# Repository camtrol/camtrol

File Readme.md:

# 캠트롤 Folder back up..

### 1. 2025-03-09-20:42 커밋 내용

- 조명 콘트롤러 저전압 회로 추가.
- 조명 콘트롤러 ST7735 추가.
- 조명 콘트롤러 저전압 진입 동작 추가 (comSend 로 BAT_LOW 보냄) -> while 반복
- 조명 콘트롤러 7" 프로그램 수정 -> BAT_LOW 수신하여 처리.

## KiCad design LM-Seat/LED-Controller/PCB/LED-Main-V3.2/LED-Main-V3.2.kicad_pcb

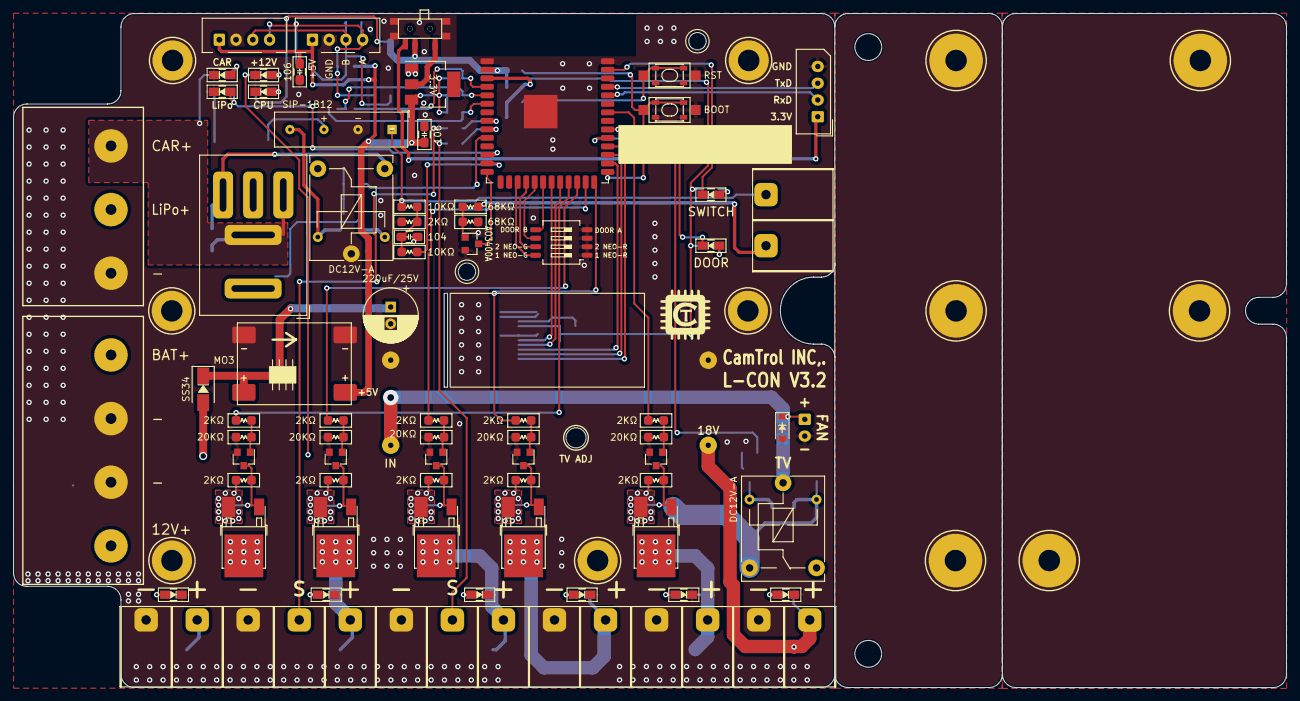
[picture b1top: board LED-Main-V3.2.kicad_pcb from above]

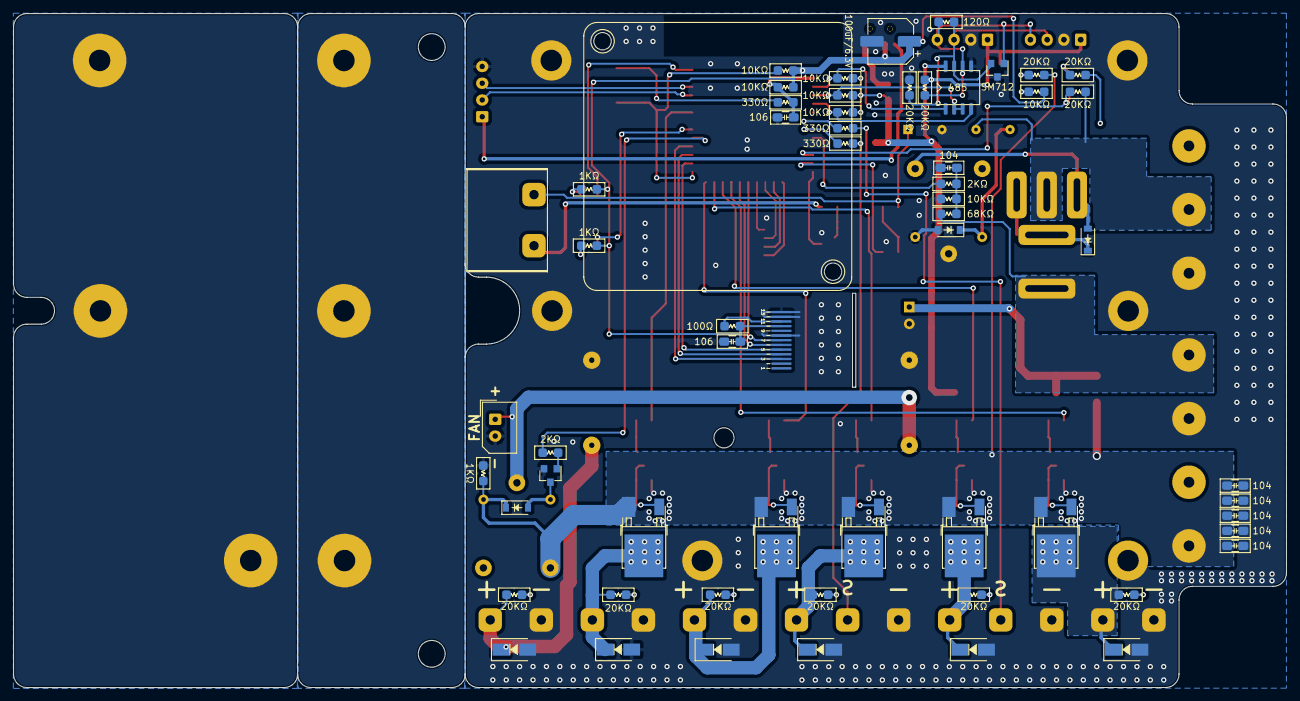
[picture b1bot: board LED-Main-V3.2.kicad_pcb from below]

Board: 2 copper layers, 190.0 x 100.6 mm, 140 parts (57 on the bottom side), 85 nets.

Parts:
C1: 100uF/6.3V; CP_Elec_6.3x5.3
C2, C3, C5, C12: 106; C_0805_HandSoldering
C4: 220uF/25V; CP_Radial_D8.0mm_P2.50mm
C6, C7, C8, C9, C10, C11, C13: 104; C_0805_HandSoldering
D1: CPU; LED_0805
D2, D8, D10, D11, D15, D17, D23, D28: RED LED; LED_0805
D3, D9, D12, D13, D18, D29: 4007; D_SMA
D4, D7, D16, D19: 4007; D_SOD-123
D5: SS34; D_SMA
D6: +12V; LED_0805
D20: LiPo; LED_0805
D21: CAR; LED_0805
D25: SM712; SOT-23
H1, H8, H9, H10, H12: MH; MountingHole_3.2mm_M3-support
H2, H3, H4, H5, H6, H7: MH; MountingHole_3.2mm_M3-pcb
He1: MH; MountingHole_3.2mm_M3-support
J1: 5267-04P; Molex_SPOX_5267-04A_1x04_P2.50mm_Vertical
J2: Conn_01x14_Pin; KF7.62-14P
J3: Conn_01x02_Pin; KF7.62-2P
J4, J11: 5267-04P; XH2.54-4P
J7: 5267-04P; HB-9500-4P
J9: ECH381V-2P; Molex_SPOX_5267-02A_1x02_P2.50mm_Vertical
J15: Conn_01x03_Pin; HB-9500-3P
K1: SIP-1B12; Relay_SPST_StandexMeder_SIL_Form1A
K3, K5: DC12V-A; JQC-T78-DC12V-C
K6: Relay_25A
M1: Fan; 4010-FAN
MO2: STEP-UP
MO3: MP1584; TZT-SMD
Q1, Q2, Q6, Q7, Q10, Q11, Q12, Q13, Q19, Q20: AOD4185; AOD1485
Q3, Q5, Q8, Q9, Q17, Q18: MMBTA42L; SOT-23
Q16: AO3400A; SOT-23
R1, R2, R4, R27, R31, R38, R41, R42, R43: 10KΩ; R_0805_HandSoldering
R3, R24, R26: 330Ω; R_0805_HandSoldering
R5, R8, R9, R14, R16, R17, R20, R21, R29, R30, R37, R52, R54: 2KΩ; R_0805_HandSoldering
R6, R7, R10, R13, R15, R18, R19, R22, R23, R28, R35, R39, R44, R46, R53, R55: 20KΩ; R_0805_HandSoldering
R11, R12, R48: 1KΩ; R_0805_HandSoldering
R25: 100Ω; R_0805_HandSoldering
R32, R33, R47: 68KΩ; R_0805_HandSoldering
R45: 120Ω; R_0805_HandSoldering
ST7735S1: Conn_01x12_Male; ST7735S_IPS
SW2, SW5: SW_Push; TS-3404
SW3: RST; SW_SPST_CK_RS282G05A3
SW4: BOOT; SW_SPST_CK_RS282G05A3
SW7: YSS-1203; SW_DIP_SPSTx04_Slide_Copal_CHS-04A_W5.08mm_P1.27mm_JPin
SW8: NW3-SK-02
U1: 3.3V; SOT-223
U2: ESP32-S3-PCB
U4: 485; MAX485

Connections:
3V3: C1.1, C5.1, R1.1, R2.1, R4.2, R12.1, R25.1, R48.1, ST7735S1.10, SW8.2 (B), U2.2 (3V3)
+5V: C3.1, C12.1, J4.1, J11.1, MO3.4 (+5V), R41.2, R42.2, R43.2, R46.1, U1.3 (VI), U4.8 (VCC)
+12P: C6.2, C7.2, C8.2, C9.2, C10.2, D5.1 (A), D16.2 (K), J7.4, K3.6, K3.14, Q1.S (Source), Q2.S (Source), Q6.S (Source), Q7.S (Source), Q10.S (Source), Q11.S (Source), Q12.S (Source), Q13.S (Source), Q19.S (Source), Q20.S (Source), R5.1, R10.1, R11.2, R14.1, R20.1, R21.1, R54.1
/485-A: D25.1 (A1), J4.4, J11.4, R45.1, R46.2, U4.6 (A)
/485-B: D25.2 (A2), J4.3, J11.3, R44.1, R45.2, U4.7 (B)
/+: J15.2, K1.5, K6.87A, R35.1
BAT +: J7.1, K6.30, R47.2
BOOT: R4.1, SW4.1, SW5.2, U2.27 (IO_0)
DI: R41.1, U2.6 (IO_6), U4.4 (DI)
DOOR: Q16.3 (D), U2.14 (IO_20)
EN: C2.1, R2.2, R3.1, U2.3 (EN)
ENABLE: R42.1, U2.5 (IO_5), U4.2 (~RE), U4.3 (DE)
FLOOR: R52.2, U2.34 (TDI/IO_41)
GNDPWR: C1.2, C2.2, C3.2, C4.2, C5.2, C6.1, C7.1, C8.1, C9.1, C10.1, C11.2, C12.2, C13.2, D1.1 (K), D2.1 (K), D3.1 (A), D4.1 (A), D6.1 (K), D8.1 (K), D9.1 (A), D10.1 (K), D11.1 (K), D12.1 (A), D13.1 (A), D17.1 (K), D18.1 (A), D19.1 (A), D20.1 (K), D21.1 (K), D25.3 (common), D28.1 (K), D29.1 (A), H2.1, H3.1, H4.1, H5.1, H6.1, H7.1, J1.4, J2.1, J2.3, J2.6, J2.9, J2.11, J2.13, J4.2, J7.2, J7.3, J9.2, J11.2, J15.3, K1.3, K5.2, K5.7, MO2.1 (GND), MO2.3 (GND), MO3.1 (GND), MO3.3 (GND), Q3.2 (E), Q5.2 (E), Q8.2 (E), Q9.2 (E), Q16.2 (S), Q17.2 (E), Q18.2 (E), R7.2, R11.1, R13.2, R18.2, R19.2, R30.1, R33.1, R38.1, R44.2, R53.2, ST7735S1.8, ST7735S1.12, ST7735S1.13, SW2.1, SW3.2, SW4.2, SW5.1, SW7.1, SW7.2, SW7.3, SW7.4, SW8.4 (C), U1.1 (GND), U2.1 (GND), U2.40 (GND), U2.41 (GND), U4.5 (GND)
IPS-CS: ST7735S1.6, U2.22 (IO_14)
IPS-RESET: ST7735S1.7, U2.21 (IO_13)
IPS-RS: ST7735S1.5, U2.28 (IO_35)
IPS-SCL: ST7735S1.4, U2.29 (IO_36)
IPS-SDA: ST7735S1.3, U2.30 (IO_37)
LED_1: R8.2, U2.23 (IO_21)
LED_2: R9.2, U2.24 (IO_47)
LED_3: R16.2, U2.25 (IO_48)
LED_4: R17.2, U2.26 (IO_45)
LiPo: D20.2 (A), R35.2, U2.12 (IO_8)
NEO_1: R24.2, U2.8 (IO_15)
NEO_2: R26.2, U2.9 (IO_16)
unnamed: C11.1, R27.1, R30.2, R31.2
unnamed: C13.1, R37.1, R38.2, R47.1
unnamed: D1.2 (A), R1.2
unnamed: D2.2 (A), R6.2
unnamed: D3.2 (K), J2.2, Q1.D (Drain), Q2.D (Drain), R6.1
unnamed: D4.2 (K), J9.1, K3.7, MO2.2 (+12V)
unnamed: C4.1, D5.2 (K), MO3.2 (+12V)
unnamed: D6.2 (A), R10.2
unnamed: D7.1 (A), K5.14, K6.86
unnamed: D7.2 (K), J15.1, K6.85, K6.87, R39.1
unnamed: D8.2 (A), R15.2
unnamed: D9.2 (K), J2.5, Q6.D (Drain), Q7.D (Drain), R15.1
unnamed: D10.2 (A), R22.2
unnamed: D11.2 (A), R23.2
unnamed: D12.2 (K), J2.8, Q10.D (Drain), Q11.D (Drain), R22.1
unnamed: D13.2 (K), J2.10, Q12.D (Drain), Q13.D (Drain), R23.1
unnamed: D15.2 (A), R12.2
unnamed: D15.1 (K), U2.39 (IO_1)
unnamed: D16.1 (A), K3.2, Q17.3 (C)
unnamed: D17.2 (A), R28.2
unnamed: D19.2 (K), K1.7, K5.6
unnamed: D21.2 (A), R39.2
unnamed: D23.2 (A), R48.2
unnamed: D23.1 (K), U2.32 (TCK/IO_39)
unnamed: D28.2 (A), R55.2
unnamed: D29.2 (K), J2.12, Q19.D (Drain), Q20.D (Drain), R55.1
unnamed: H1.1, H8.1, H9.1
unnamed: H10.1, H12.1, He1.1
unnamed: J1.1, SW8.3 (C)
unnamed: J2.4, R24.1
unnamed: J2.7, R26.1
unnamed: J3.1, R32.2
unnamed: J3.2, K1.1, R27.2
unnamed: Q1.G (Gate), Q2.G (Gate), Q3.3 (C), R5.2
unnamed: Q3.1 (B), R7.1, R8.1
unnamed: Q5.1 (B), R9.1, R13.1
unnamed: Q5.3 (C), Q6.G (Gate), Q7.G (Gate), R14.2
unnamed: Q8.1 (B), R16.1, R18.1
unnamed: Q9.1 (B), R17.1, R19.1
unnamed: Q8.3 (C), Q10.G (Gate), Q11.G (Gate), R20.2
unnamed: Q9.3 (C), Q12.G (Gate), Q13.G (Gate), R21.2
unnamed: Q16.1 (G), R32.1, R33.2
unnamed: Q17.1 (B), R29.1
unnamed: Q18.1 (B), R52.1, R53.1
unnamed: Q18.3 (C), Q19.G (Gate), Q20.G (Gate), R54.2
unnamed: R3.2, SW2.2, SW3.1
unnamed: R25.2, ST7735S1.11
unnamed: SW8.1 (A), U1.2 (VO)
unnamed: SW7.8, U2.17 (IO_09)
unnamed: SW7.7, U2.18 (IO_10)
unnamed: SW7.6, U2.19 (IO_11)
unnamed: SW7.5, U2.20 (IO_12)
unnamed: R37.2, U2.10 (IO_17)
RO: R43.1, U2.4 (IO_4), U4.1 (RO)
RxD0: J1.2, U2.36 (RxD0)
SWITCH: R31.1, U2.13 (IO_19)
TV: R29.2, U2.31 (IO_38)
TV OUT: D18.2 (K), J2.14, MO2.4 (+18V), R28.1
TxD0: J1.3, U2.37 (TxD0)

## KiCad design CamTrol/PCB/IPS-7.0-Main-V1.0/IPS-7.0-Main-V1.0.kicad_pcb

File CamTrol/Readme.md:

# 카인드 캠핑카 메인 콘트롤러
### 1. 버전 : V3.0

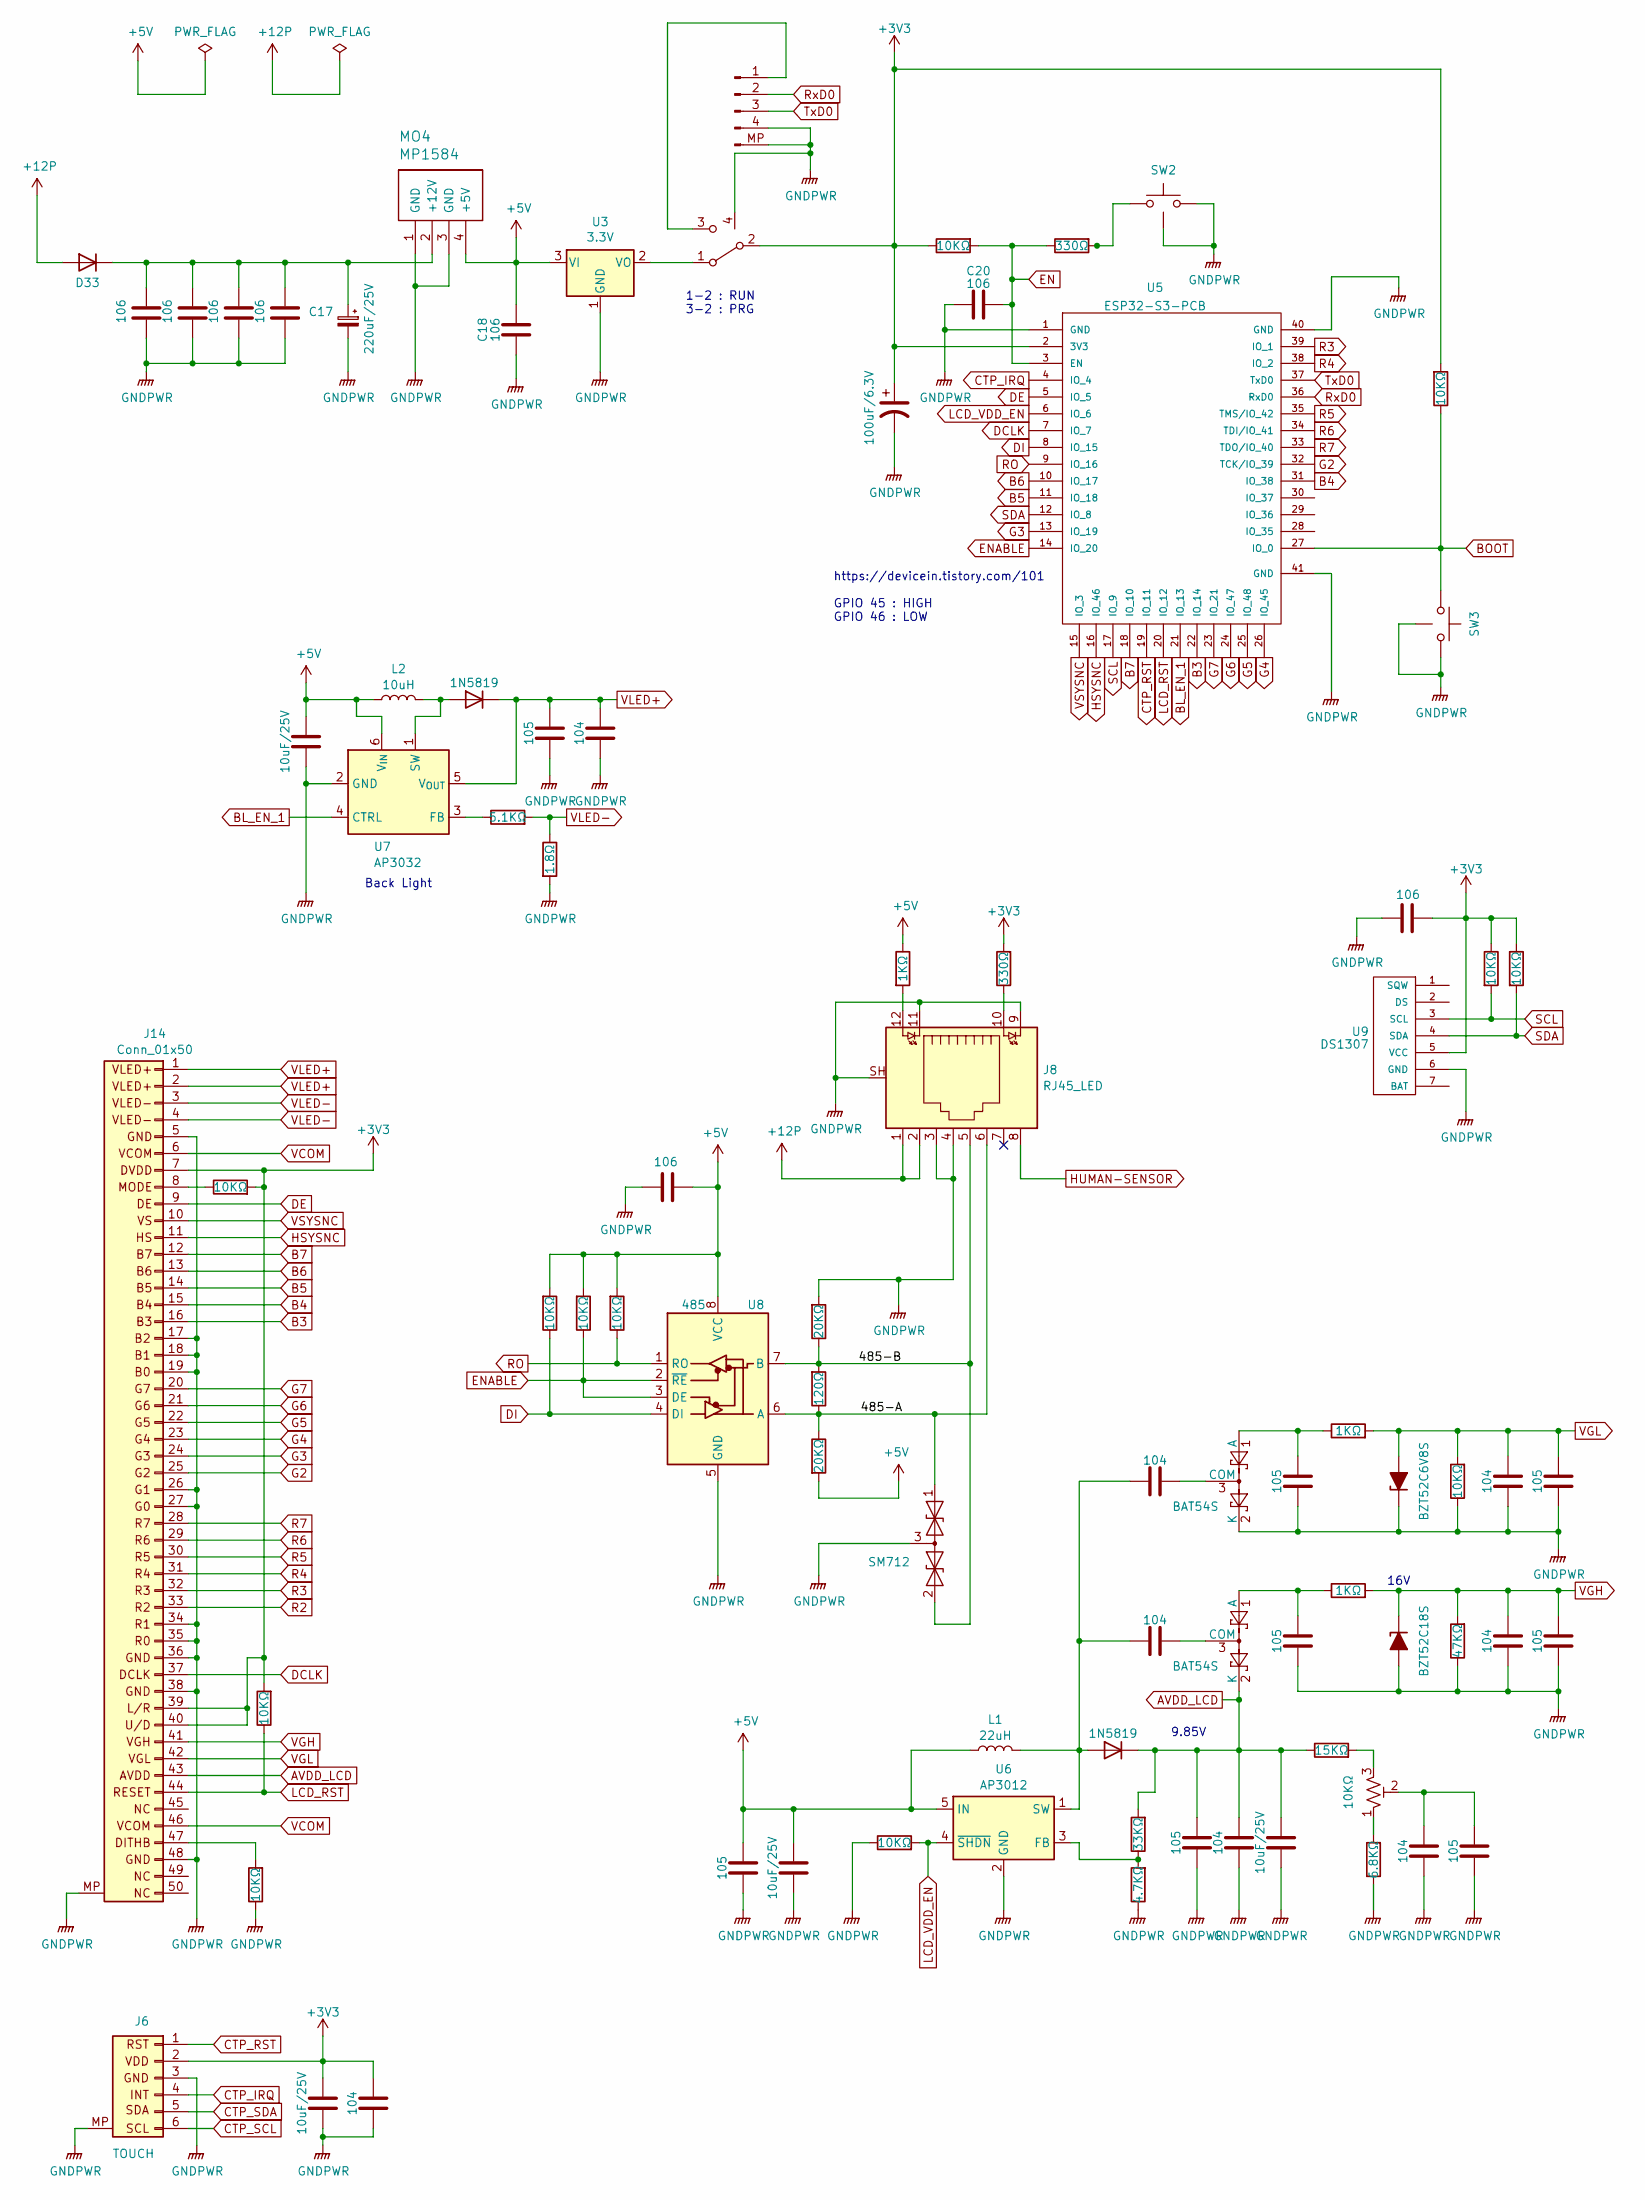
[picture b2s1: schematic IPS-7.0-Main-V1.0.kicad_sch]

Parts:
AUX_BT1: 10KΩ; Potentiometer_Bourns_TC33X_Vertical
C1, C2, C3, C4, C15, C18, C20, C38: 106; C_0805_HandSoldering
C13, C30, C34, C35: 10uF/25V; CP_Elec_6.3x3
C14, C21, C23, C24, C26, C29, C31, C37: 104; C_0805_HandSoldering
C16, C22, C25, C27, C28, C32, C33, C36: 105; C_0805_HandSoldering
C17: 220uF/25V; CP_Radial_D8.0mm_P2.50mm
C19: 100uF/6.3V; CP_Elec_6.3x5.3
D28: SM712; SOT-23
D30: BZT52C6V8S; D_SOD-323_HandSoldering
D31: BZT52C18S; D_SOD-323_HandSoldering
D32, D34: BAT54S; SOT-23
D33: SS34; D_SMA
D35, D37: 1N5819; D_SMA
J1: Conn_01x04_Pin; JST_GH_SM04B-GHS-TB_1x04-1MP_P1.25mm_Horizontal
J6: TOUCH; Hirose_FH12-6S-0.5SH_1x06-1MP_P0.50mm_Horizontal
J8: RJ45_LED; RJ45_LED_SMD
J14: Conn_01x50; Hirose_FH12-50S-0.5SH_1x50-1MP_P0.50mm_Horizontal
L1: 22uH; CD43
L2: 10uH; CD43
MO4: MP1584; TZT-SMD
R37, R38, R47, R50, R52, R56, R59, R60, R61, R67, R68, R69: 10KΩ; R_0805_HandSoldering
R51, R53, R73: 1KΩ; R_0805_HandSoldering
R54: 47KΩ; R_0805_HandSoldering
R57: 15KΩ; R_0805_HandSoldering
R58, R74: 330Ω; R_0805_HandSoldering
R62: 6.8KΩ; R_0805_HandSoldering
R63: 33KΩ; R_0805_HandSoldering
R64: 4.7KΩ; R_0805_HandSoldering
R65: 5.1KΩ; R_0805_HandSoldering
R66: 1.8Ω; R_0805_HandSoldering
R70, R72: 20KΩ; R_0805_HandSoldering
R71: 120Ω; R_0805_HandSoldering
SW1: NW3-SK-02
SW2, SW3: SW_Push; MP3-2x4x3.5mm-TACT
U3: 3.3V; SOT-223
U5: ESP32-S3-PCB
U6: AP3012; SOT-23-5
U7: AP3032; SOT-23-6
U8: 485; MAX485
U9: DS1307

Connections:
+3V3: C13.1, C14.1, C19.1, C38.1, J6.2, J14.7, J14.39, J14.40, R56.1, R59.2, R60.1, R61.1, R67.2, R68.2, R74.2, SW1.2 (B), U5.2 (3V3), U9.5 (VCC)
+5V: C15.1, C18.1, C33.1, C34.1, C35.1, L1.1, L2.1, MO4.4 (+5V), R37.2, R38.2, R47.2, R72.2, R73.1, U3.3 (VI), U6.5 (IN), U7.6 (V_{IN}), U8.8 (VCC)
+12P: D33.1 (A), J8.1, J8.2
/485-A: D28.1 (A1), J8.6, R71.1, R72.1, U8.6 (A)
/485-B: D28.2 (A2), J8.5, R70.1, R71.2, U8.7 (B)
AVDD_LCD: C28.1, C29.1, C30.1, D34.2 (K), D35.2 (K), J14.43, R57.1, R63.2
B3: J14.16, U5.22 (IO_14)
B4: J14.15, U5.31 (IO_38)
B5: J14.14, U5.11 (IO_18)
B6: J14.13, U5.10 (IO_17)
B7: J14.12, U5.18 (IO_10)
BL_EN_1: U5.21 (IO_13), U7.4 (CTRL)
BOOT: R59.1, SW3.2, U5.27 (IO_0)
CTP_IRQ: J6.4, U5.4 (IO_4)
CTP_RST: J6.1, U5.19 (IO_11)
CTP_SCL: J6.6
CTP_SDA: J6.5
DCLK: J14.37, U5.7 (IO_7)
DE: J14.9, U5.5 (IO_5)
DI: R37.1, U5.8 (IO_15), U8.4 (DI)
EN: C20.1, R56.2, R58.1, U5.3 (EN)
ENABLE: R38.1, U5.14 (IO_20), U8.2 (~RE), U8.3 (DE)
G2: J14.25, U5.32 (TCK/IO_39)
G3: J14.24, U5.13 (IO_19)
G4: J14.23, U5.26 (IO_45)
G5: J14.22, U5.25 (IO_48)
G6: J14.21, U5.24 (IO_47)
G7: J14.20, U5.23 (IO_21)
GNDPWR: C1.1, C2.1, C3.1, C4.1, C13.2, C14.2, C15.2, C16.2, C17.2, C18.2, C19.2, C20.2, C21.2, C22.2, C25.2, C26.2, C27.2, C28.2, C29.2, C30.2, C31.2, C32.2, C33.2, C34.2, C35.2, C36.2, C37.2, C38.2, D28.3 (common), D30.1 (K), D31.2 (A), D32.2 (K), J1.4, J1.MP (Pin_5), J6.3, J6.MP (Pin_6), J8.3, J8.4, J8.9, J8.11, J8.SH, J14.5, J14.17, J14.18, J14.19, J14.26, J14.27, J14.34, J14.35, J14.36, J14.38, J14.48, J14.MP (Pin_50), MO4.1 (GND), MO4.3 (GND), R50.1, R52.1, R54.1, R62.1, R64.1, R66.2, R69.1, R70.2, SW1.4 (C), SW2.1, SW2.MP, SW3.1, SW3.MP, U3.1 (GND), U5.1 (GND), U5.40 (GND), U5.41 (GND), U6.2 (GND), U7.2 (GND), U8.5 (GND), U9.6 (GND); also elsewhere on the board
HSYSNC: J14.11, U5.16 (IO_46)
HUMAN-SENSOR: J8.8
LCD_RST: J14.44, R67.1, U5.20 (IO_12)
LCD_VDD_EN: R50.2, U5.6 (IO_6), U6.4 (~SHDN)
unnamed: AUX_BT1.1, R62.2
unnamed: AUX_BT1.2, C31.1, C32.1
unnamed: AUX_BT1.3, R57.2
unnamed: C16.1, D32.1 (A), R51.1
unnamed: C23.2, D32.3 (COM)
unnamed: C1.2, C2.2, C3.2, C4.2, C17.1, D33.2 (K), MO4.2 (+12V)
unnamed: C25.1, D34.1 (A), R53.1
unnamed: C24.2, D34.3 (COM)
unnamed: C23.1, C24.1, D35.1 (A), L1.2, U6.1 (SW)
unnamed: D37.1 (A), L2.2, U7.1 (SW)
unnamed: J1.1, SW1.3 (C)
unnamed: J8.10, R74.1
unnamed: J8.12, R73.2
unnamed: J14.8, R68.1
unnamed: J14.47, R69.2
unnamed: R58.2, SW2.2
unnamed: SW1.1 (A), U3.2 (VO)
unnamed: R63.1, R64.2, U6.3 (FB)
unnamed: R65.1, U7.3 (FB)
R2: J14.33
R3: J14.32, U5.39 (IO_1)
R4: J14.31, U5.38 (IO_2)
R5: J14.30, U5.35 (TMS/IO_42)
R6: J14.29, U5.34 (TDI/IO_41)
R7: J14.28, U5.33 (TDO/IO_40)
RO: R47.1, U5.9 (IO_16), U8.1 (RO)
RxD0: J1.2, U5.36 (RxD0)
SCL: R60.2, U5.17 (IO_9), U9.3 (SCL)
SDA: R61.2, U5.12 (IO_8), U9.4 (SDA)
TxD0: J1.3, U5.37 (TxD0)
VCOM: J14.6, J14.46
VGH: C26.1, C27.1, D31.1 (K), J14.41, R53.2, R54.2
VGL: C21.1, C22.1, D30.2 (A), J14.42, R51.2, R52.2
VLED+: C36.1, C37.1, D37.2 (K), J14.1, J14.2, U7.5 (V_{OUT})
VLED-: J14.3, J14.4, R65.2, R66.1
VSYSNC: J14.10, U5.15 (IO_3)

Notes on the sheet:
16V
Back Light
https://devicein.tistory.com/101 GPIO 45 : HIGH GPIO 46 : LOW
1-2 : RUN 3-2 : PRG
9.85V

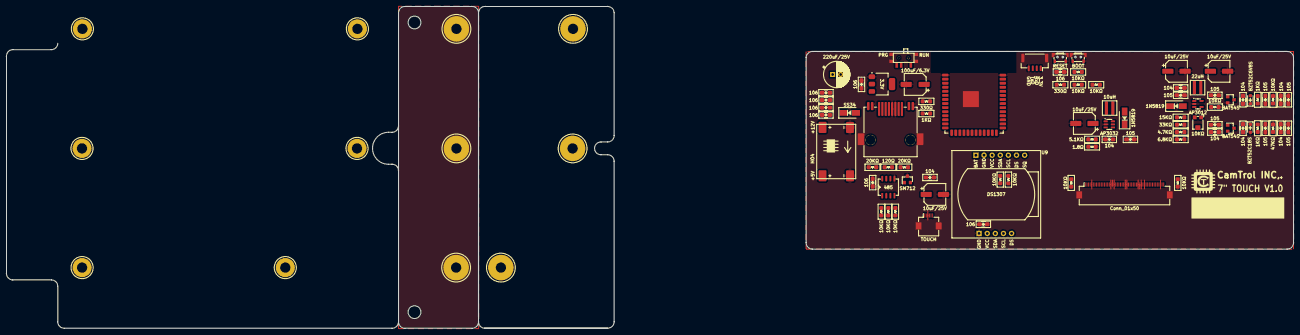
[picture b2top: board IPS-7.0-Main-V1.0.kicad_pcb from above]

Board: 2 copper layers, 152.4 x 61.8 mm, 94 parts (0 on the bottom side), 67 nets.

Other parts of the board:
H1, H8, H9, H10, H12: MH; MountingHole_3.2mm_M3-support
H2, H3, H4, H5, H6, H7: MH; MountingHole_3.2mm_M3-pcb
He1: MH; MountingHole_3.2mm_M3-support

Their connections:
GNDPWR: H2.1, H3.1, H4.1, H5.1, H6.1, H7.1; also elsewhere on the board
unnamed: H1.1, H8.1, H9.1
unnamed: H10.1, H12.1, He1.1

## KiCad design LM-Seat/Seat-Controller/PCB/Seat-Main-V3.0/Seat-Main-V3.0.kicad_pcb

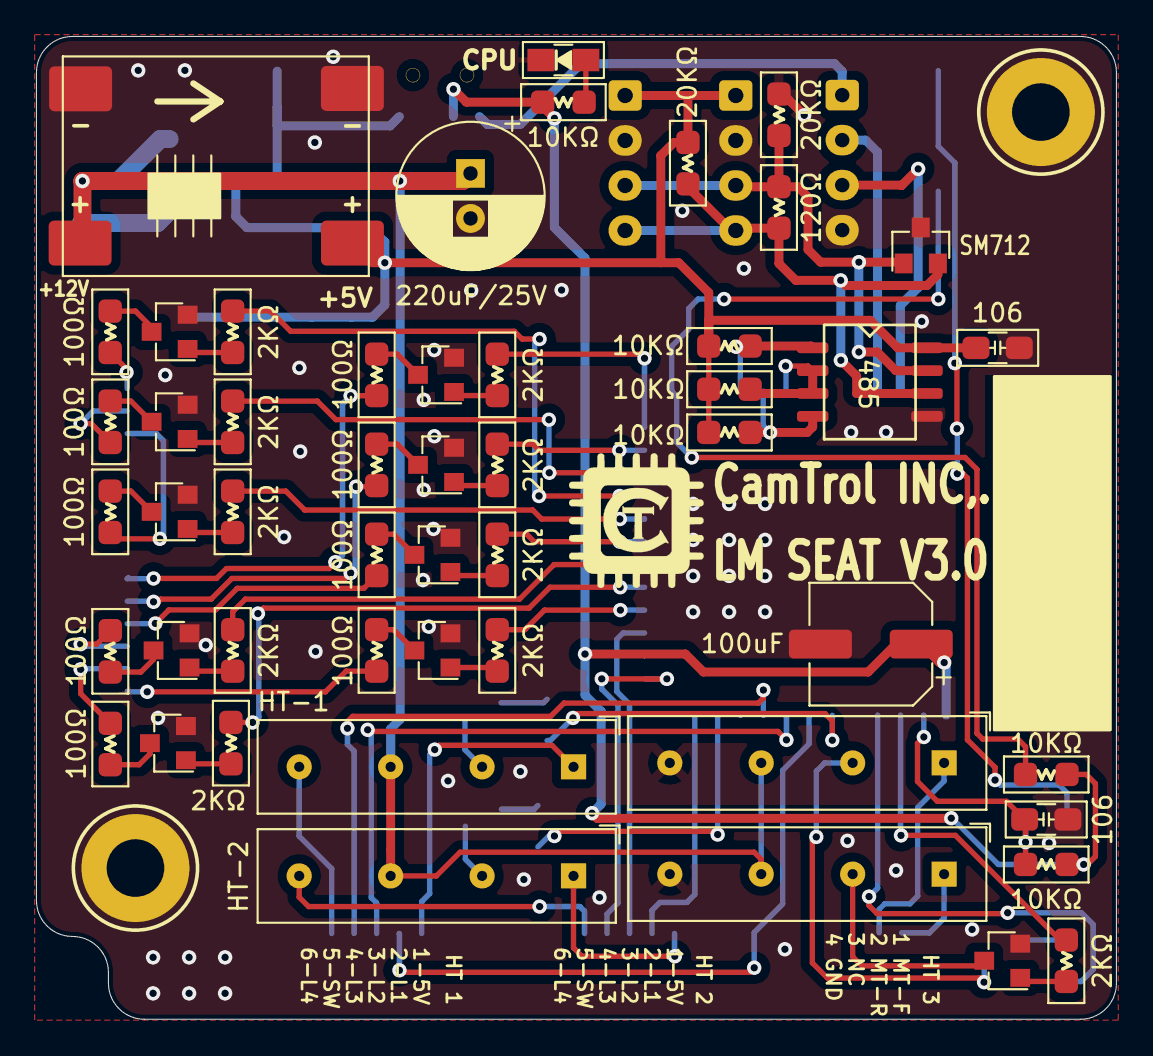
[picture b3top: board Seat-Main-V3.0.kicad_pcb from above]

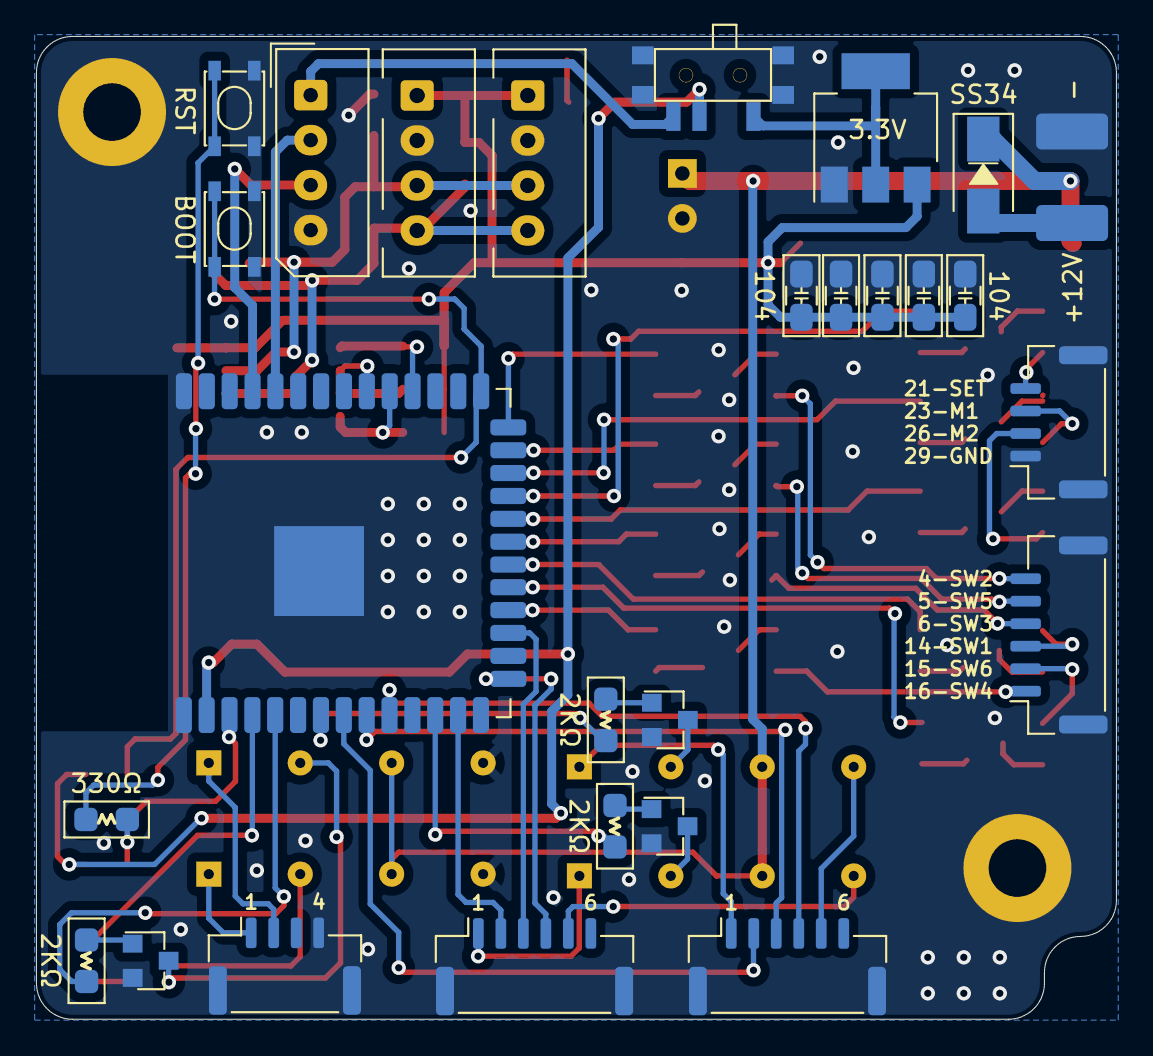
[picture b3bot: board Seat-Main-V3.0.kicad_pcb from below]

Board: 2 copper layers, 60.0 x 54.6 mm, 80 parts (28 on the bottom side), 78 nets.

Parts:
C2, C4, C5, C6, C7: 104; C_0805_HandSoldering
C3, C10: 106; C_0805_HandSoldering
C8: 220uF/25V; CP_Radial_D8.0mm_P2.50mm
C9: 100uF; CP_Elec_6.3x5.3
D1: SS34; D_SMA
D2: CPU; LED_0805
D3: SM712; SOT-23
H1, H2: MH; MountingHole_3.2mm_M3-pcb
J1, J2: Conn_01x01_Pin; SMD_CONN_1x01_P2.50mm
J3, J05, J8: Conn_01x06_Pin; JST_GH_SM06B-GHS-TB_1x06-1MP_P1.25mm_Horizontal
J4: 5267-04P; Molex_SPOX_5267-04A_1x04_P2.50mm_Vertical
J6, J9: 5267-04P; JST_GH_SM04B-GHS-TB_1x04-1MP_P1.25mm_Horizontal
J7, J11: 5267-04P; XH2.54-4P
K1, K6: HT-1; Relay_SPST_StandexMeder_SIL_Form1A
K2, K5: HT-2; Relay_SPST_StandexMeder_SIL_Form1A
MO2: MP1584; TZT-SMD
Q1, Q2, Q3, Q4, Q5, Q6, Q7, Q8, Q9, Q10, Q11, Q12, Q13: MMBTA42L; SOT-23
R1, R6, R7, R8, R9, R13, R14, R16, R18, R22, R24, R25, R26: 2KΩ; R_0805_HandSoldering
R2, R3, R5, R41, R42, R43: 10KΩ; R_0805_HandSoldering
R4: 330Ω; R_0805_HandSoldering
R10, R11, R12, R15, R17, R19, R20, R21, R23: 100Ω; R_0805_HandSoldering
R44, R46: 20KΩ; R_0805_HandSoldering
R45: 120Ω; R_0805_HandSoldering
SW2: NW3-SK-02
SW3: RST; TS-3404
SW6: BOOT; TS-3404
U1: 3.3V; SOT-223
U2: ESP32-S3-PCB
U4: 485; MAX485

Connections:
3V3: C9.1, R2.1, R3.1, R5.2, SW2.2 (B), U2.2 (3V3)
+5V: C2.2, C3.1, C4.2, C5.2, C6.2, C7.2, J7.1, J11.1, MO2.4 (+5V), R41.2, R42.2, R43.2, R46.1, U1.3 (VI), U4.8 (VCC)
/485-A: D3.2 (A2), J7.4, J11.4, R45.1, R46.2, U4.6 (A)
/485-B: D3.1 (A1), J7.3, J11.3, R44.1, R45.2, U4.7 (B)
/M 1: J6.3, R11.1
/M 2: J6.2, R12.1
/SET: J6.4, R10.1
BOOT: R5.1, SW6.2, U2.27 (IO_0)
DI: R41.1, U2.31 (IO_38), U4.4 (DI)
EN: C10.1, R3.2, R4.1, U2.3 (EN)
ENABLE: R42.1, U2.32 (TCK/IO_39), U4.2 (~RE), U4.3 (DE)
GNDPWR: C2.1, C3.2, C4.1, C5.1, C6.1, C7.1, C8.2, C9.2, C10.2, D2.1 (K), D3.3 (common), H1.1, H2.1, J2.1, J3.MP (Pin_7), J4.4, J05.MP (Pin_7), J6.1, J6.MP (Pin_5), J7.2, J8.MP (Pin_7), J9.4, J9.MP (Pin_5), J11.2, K5.7, K6.7, MO2.1 (GND), MO2.3 (GND), Q1.2 (E), Q2.2 (E), Q3.2 (E), Q4.2 (E), Q5.2 (E), Q6.2 (E), Q7.2 (E), Q8.2 (E), Q9.2 (E), Q10.2 (E), Q11.2 (E), Q12.2 (E), Q13.2 (E), R44.2, SW2.4 (C), SW3.1, SW6.1, U1.1 (GND), U2.1 (GND), U2.40 (GND), U2.41 (GND), U4.5 (GND)
H1-L1: J3.2, U2.8 (IO_15)
H1-L2: J3.3, U2.9 (IO_16)
H1-L3: J3.4, U2.10 (IO_17)
H2-L1: J05.2, U2.13 (IO_19)
H2-L2: J05.3, U2.17 (IO_09)
H2-L3: J05.4, U2.15 (IO_3)
H-M1: R8.2, U2.24 (IO_47)
H-M2: R9.2, U2.22 (IO_14)
H-SET: R1.2, U2.23 (IO_21)
HEATER 1: R6.2, U2.7 (IO_7)
HEATER 2: R7.2, U2.12 (IO_8)
MT-F: R25.2, U2.4 (IO_4)
MT-R: R26.2, U2.5 (IO_5)
unnamed: D1.1 (A), J1.1
unnamed: C8.1, D1.2 (K), K1.5, K2.5, K5.5, K6.5, MO2.2 (+12V)
unnamed: D2.2 (A), R2.2
unnamed: J3.1, K1.1
unnamed: J3.5, K1.7
unnamed: J4.1, SW2.3 (C)
unnamed: J05.1, K2.1
unnamed: J05.5, K2.7
unnamed: J8.1, R23.1
unnamed: J8.2, R21.1
unnamed: J8.3, R17.1
unnamed: J8.4, R15.1
unnamed: J8.5, R20.1
unnamed: J8.6, R19.1
unnamed: J9.1, K6.1
unnamed: J9.2, K5.1
unnamed: Q1.1 (B), R1.1
unnamed: Q1.3 (C), R10.2
unnamed: Q2.1 (B), R26.1
unnamed: K5.3, Q2.3 (C)
unnamed: Q3.1 (B), R25.1
unnamed: K6.3, Q3.3 (C)
unnamed: Q4.1 (B), R8.1
unnamed: Q4.3 (C), R11.2
unnamed: Q5.1 (B), R9.1
unnamed: Q5.3 (C), R12.2
unnamed: Q6.1 (B), R13.1
unnamed: Q6.3 (C), R19.2
unnamed: Q7.1 (B), R14.1
unnamed: Q7.3 (C), R20.2
unnamed: Q8.1 (B), R16.1
unnamed: Q8.3 (C), R15.2
unnamed: Q9.1 (B), R18.1
unnamed: Q9.3 (C), R17.2
unnamed: Q10.1 (B), R22.1
unnamed: Q10.3 (C), R21.2
unnamed: Q11.1 (B), R24.1
unnamed: Q11.3 (C), R23.2
unnamed: Q12.1 (B), R6.1
unnamed: K1.3, Q12.3 (C)
unnamed: Q13.1 (B), R7.1
unnamed: K2.3, Q13.3 (C)
unnamed: R4.2, SW3.2
unnamed: SW2.1 (A), U1.2 (VO)
RO: R43.1, U2.30 (IO_37), U4.1 (RO)
RxD0: J4.2, U2.36 (RxD0)
SW 1: R13.2, U2.26 (IO_45)
SW 2: R14.2, U2.25 (IO_48)
SW 3: R16.2, U2.21 (IO_13)
SW 4: R18.2, U2.20 (IO_12)
SW 5: R22.2, U2.19 (IO_11)
SW 6: R24.2, U2.18 (IO_10)
TxD0: J4.3, U2.37 (TxD0)

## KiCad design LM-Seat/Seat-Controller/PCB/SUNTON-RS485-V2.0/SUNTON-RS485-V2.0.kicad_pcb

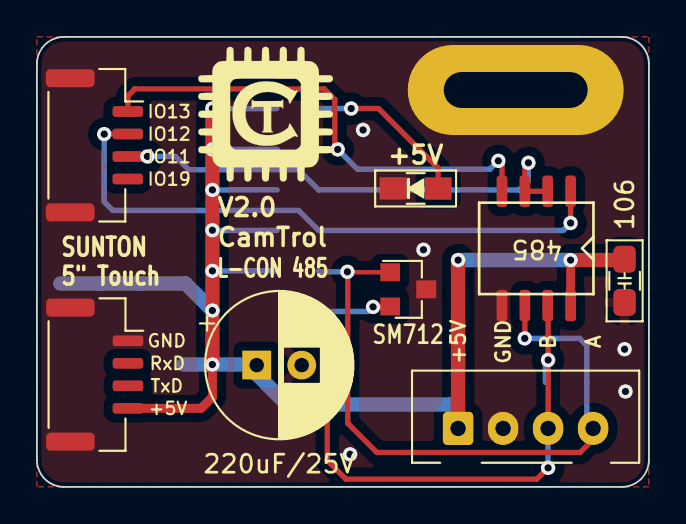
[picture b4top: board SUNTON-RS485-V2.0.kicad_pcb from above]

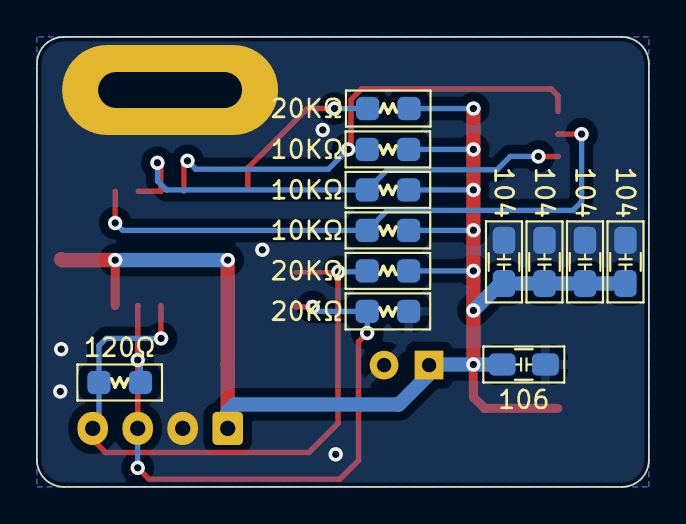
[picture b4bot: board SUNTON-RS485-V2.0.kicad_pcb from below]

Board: 2 copper layers, 34.0 x 25.0 mm, 21 parts (12 on the bottom side), 8 nets.

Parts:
C1, C3: 106; C_0805_HandSoldering
C2, C4, C5, C6: 104; C_0805_HandSoldering
C7: 220uF/25V; CP_Radial_D8.0mm_P2.50mm
D1: SM712; SOT-23
D6: +5V; LED_0805
J1, J4: Conn_01x04_Pin; JST_GH_SM04B-GHS-TB_1x04-1MP_P1.25mm_Horizontal
J3: Conn_01x01_Pin; LM-CON-PAD
J11: 5267-04P; XH2.54-4P
R10, R44, R46: 20KΩ; R_0805_HandSoldering
R41, R42, R43: 10KΩ; R_0805_HandSoldering
R45: 120Ω; R_0805_HandSoldering
U4: 485; MAX485

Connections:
+5V: C1.1, C2.2, C3.1, C4.2, C5.2, C6.2, C7.1, J1.4, J11.1, R10.1, R41.2, R42.2, R43.2, R46.1, U4.8 (VCC)
/485-A: D1.1 (A1), J11.4, R45.1, R46.2, U4.6 (A)
/485-B: D1.2 (A2), J11.3, R44.1, R45.2, U4.7 (B)
GNDPWR: C1.2, C2.1, C3.2, C4.1, C5.1, C6.1, C7.2, D1.3 (common), D6.1 (K), J1.1, J1.MP (Pin_5), J3.1, J4.MP (Pin_5), J11.2, R44.2, U4.5 (GND)
unnamed: D6.2 (A), R10.2
unnamed: J4.1, R41.1, U4.4 (DI)
unnamed: J4.2, R43.1, U4.1 (RO)
unnamed: J4.3, R42.1, U4.2 (~RE), U4.3 (DE)
